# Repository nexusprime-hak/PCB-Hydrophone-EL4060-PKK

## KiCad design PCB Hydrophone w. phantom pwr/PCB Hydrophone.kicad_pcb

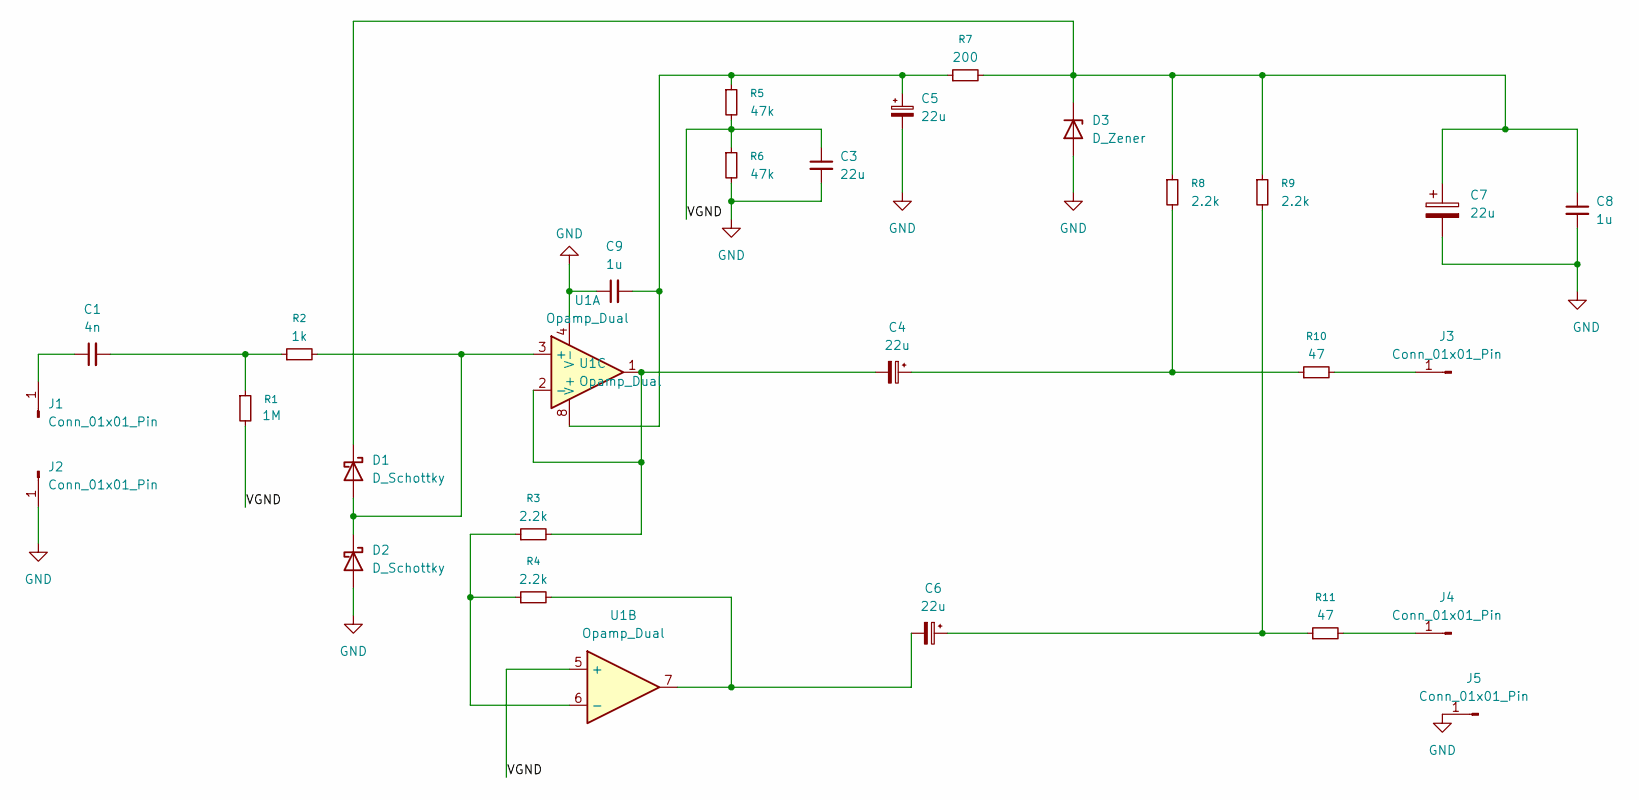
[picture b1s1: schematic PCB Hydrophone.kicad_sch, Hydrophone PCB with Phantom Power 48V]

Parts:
C1: 4n; CP_Radial_D5.0mm_P2.00mm
C3, C4, C5, C6, C7: 22u; CP_Radial_D5.0mm_P2.00mm
C8, C9: 1u; CP_Radial_D5.0mm_P2.00mm
D1: D_Schottky; D_DO-41_SOD81_P2.54mm_Vertical_AnodeUp
D2: D_Schottky; D_DO-41_SOD81_P3.81mm_Vertical_AnodeUp
D3: D_Zener; D_DO-41_SOD81_P2.54mm_Vertical_AnodeUp
J1, J2, J3, J4, J5: Conn_01x01_Pin; PinHeader_1x01_P2.54mm_Vertical
R1: 1M; R_Axial_DIN0204_L3.6mm_D1.6mm_P5.08mm_Horizontal
R2: 1k; R_Axial_DIN0204_L3.6mm_D1.6mm_P5.08mm_Horizontal
R3, R4, R8, R9: 2.2k; R_Axial_DIN0204_L3.6mm_D1.6mm_P5.08mm_Horizontal
R5, R6: 47k; R_Axial_DIN0204_L3.6mm_D1.6mm_P5.08mm_Horizontal
R7: 200; R_Axial_DIN0204_L3.6mm_D1.6mm_P5.08mm_Horizontal
R10, R11: 47; R_Axial_DIN0204_L3.6mm_D1.6mm_P5.08mm_Horizontal
U1: Opamp_Dual; SOIC-8_3.9x4.9mm_P1.27mm

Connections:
/VGND: C3.1, R1.2, R5.2, R6.1, U1.5 (+)
GND: C3.2, C5.2, C7.2, C8.2, C9.1, D2.2 (A), D3.2 (A), J2.1 (Pin_1_1), J5.1 (Pin_1_1), R6.2, U1.4 (V-)
unnamed: C1.2, R1.1, R2.1
unnamed: C4.1, R8.2, R10.1
unnamed: C6.1, R9.2, R11.1
unnamed: C6.2, R4.2, U1.7
unnamed: D1.2 (A), D2.1 (K), R2.2, U1.3 (+)
unnamed: C7.1, C8.1, D1.1 (K), D3.1 (K), R7.2, R8.1, R9.1
unnamed: C1.1, J1.1 (Pin_1_1)
unnamed: J3.1 (Pin_1_1), R10.2
unnamed: J4.1 (Pin_1_1), R11.2
unnamed: C4.2, R3.2, U1.1, U1.2 (-)
unnamed: R3.1, R4.1, U1.6 (-)
unnamed: C5.1, C9.2, R5.1, R7.1, U1.8 (V+)

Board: 2 copper layers, 28 parts (0 on the bottom side), 14 nets, no tracks yet.
